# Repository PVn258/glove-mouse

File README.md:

# Glove Mouse

A wearable BLE HID mouse built on the **XIAO ESP32-C6**, controlled by wrist movement (MPU-6050 gyroscope) and finger sensors (flex + FSR pressure).

---

## Hardware

| Component | Role |
|-----------|------|
| XIAO ESP32-C6 | Main MCU + BLE |
| MPU-6050 | Gyroscope / accelerometer → cursor movement |
| Flex sensor | Thumb bend → toggle transmission mode |
| FSR (×2) | Left / right click |
| MT3608 boost | Battery → ~4.6 V rail for VIN |
| LM339 (×2) | Analog comparators for flex & FSR digital output |

### Wiring

```
MPU-6050   SDA → GPIO 6   |   SCL → GPIO 7
Flex  DO       → GPIO 4     (thumb bend = transmit mode)
FSR Left  DO   → GPIO 2     (left click)
FSR Right DO   → GPIO 3     (right click)
```

---

## Firmware

### Dependencies (install via Arduino IDE Library Manager)

- **NimBLE-Arduino** by h2zero `≥ 1.4.0`
- **MPU6050** by Electronic Cats

### Board setup

1. Add ESP32 board package URL in Arduino IDE preferences:
   ```
   https://raw.githubusercontent.com/espressif/arduino-esp32/gh-pages/package_esp32_index.json
   ```
2. Install **esp32** by Espressif Systems
3. Select board: **XIAO ESP32C6**

### Usage

1. Flash `glove_mouse/glove_mouse.ino`
2. Open Serial Monitor at **115200 baud**
3. Pair with **"Glove Mouse"** from your host's Bluetooth settings
4. **Bend thumb** → transmission mode (cursor follows wrist, FSR triggers clicks)
5. **Release thumb** → sleep mode (all input paused)

### Tuning parameters

| Constant | Default | Description |
|----------|---------|-------------|
| `MAX_MOVE` | 20 | Max pixels per frame (higher = more sensitive) |
| `MAX_DPS` | 200 | Gyro threshold for full speed (°/s) |
| `DEADZONE` | 5 | Dead zone in °/s (higher = less jitter) |
| `CURVE_EXP` | 1.5 | Speed curve exponent (1.0 = linear, >1 = precise low / fast high) |
| `EMA_ALPHA` | 0.25 | Smoothing factor (0.1 = very smooth, 0.4 = responsive) |

---

## Schematic & PCB Design

The circuit was drawn in **EasyEDA Pro** and exported for JLCPCB fabrication.

| File | Description |
|------|-------------|
| `hardware/ProPrj_Seeed Studio XIAO ESP32C6_2026-05-12_10-11-10_2026-05-13.epro2` | EasyEDA Pro project (editable source) |
| `hardware/SCH_Schematic1_2026-05-14.pdf` | Schematic PDF (quick reference) |

**PCB specs for JLCPCB ordering:**

| Parameter | Value |
|-----------|-------|
| Layers | 2 |
| Board size | 50 × 40 mm |
| Min trace / space | 0.2 mm / 0.2 mm |
| Min via drill | 0.4 mm |
| Surface finish | HASL (lead-free) |

---

## Repository Structure

```
glove_mouse/
└── glove_mouse.ino          Main BLE HID firmware

hardware/
├── *.epro2                  EasyEDA Pro schematic & PCB project
└── *.pdf                    Exported schematic PDF

tests/
├── all_sensors_test/        All sensors combined diagnostic
├── flex_sensor_test/        Flex sensor digital output test
├── mpu6050_test/            MPU-6050 I2C + gyro/accel readout
└── pressure_sensor_test/    FSR pressure sensor test
```

---

## Running the Tests

Each folder under `tests/` is a standalone Arduino sketch.  
Open the `.ino` file in Arduino IDE, select **XIAO ESP32C6**, upload, then open Serial Monitor at **115200 baud**.

| Sketch | What it prints |
|--------|---------------|
| `mpu6050_test` | Accel XYZ + Gyro XYZ raw values |
| `flex_sensor_test` | Digital output of flex comparator (0/1) |
| `pressure_sensor_test` | Digital output of left & right FSR (0/1) |
| `all_sensors_test` | All of the above combined |

---

## License

MIT

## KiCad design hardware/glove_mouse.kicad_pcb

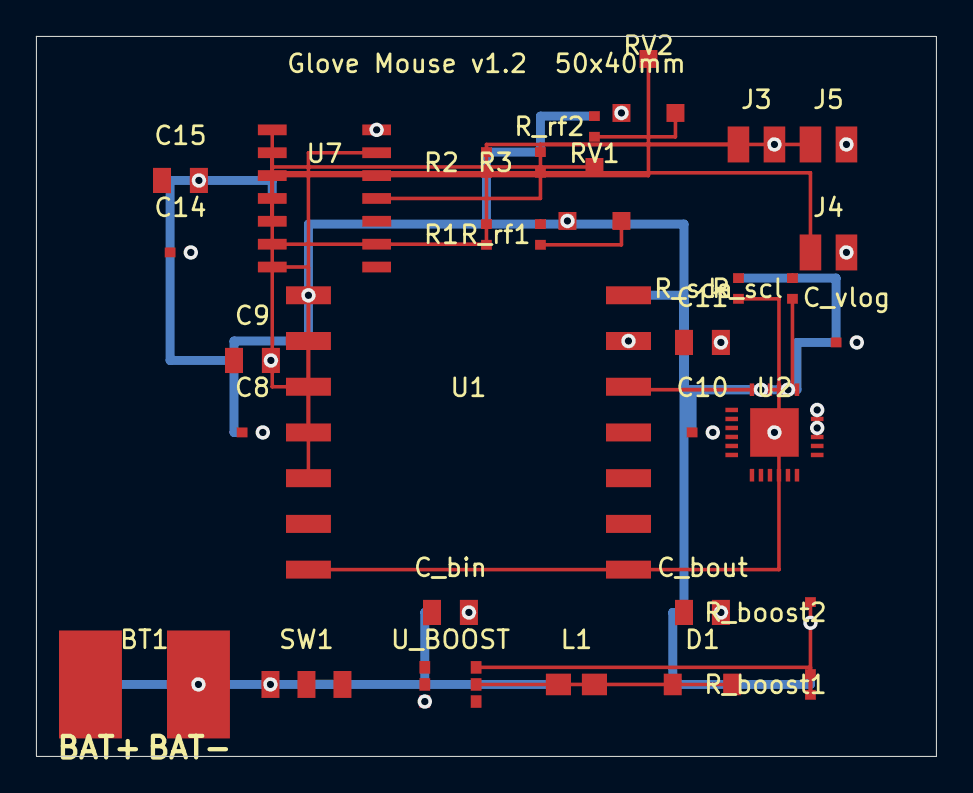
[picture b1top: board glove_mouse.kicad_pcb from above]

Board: 2 copper layers, 50.0 x 40.0 mm, 31 parts (0 on the bottom side), 19 nets.

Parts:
BT1: LiPo Battery; BAT-SOLDER
C8, C10, C14: 100nF; C_0402
C9: 22uF; C_0805
C11: 10uF; C_0805
C15: 4.7uF; C_0805
C_bin: 10uF; C_0805
C_bout: 22uF; C_0805
C_vlog: 100nF; C_0402
D1: SS14; SOD-123
J3: Flex; JST-PH-2P
J4: FSR Left; JST-PH-2P
J5: FSR Right; JST-PH-2P
L1: 4.7uH; L_0603
R1: 47k; R_0402
R2, R3: 10k; R_0402
RV1, RV2: 10k Trim; TRIMPOT-3224W
R_boost1: 100k; R_0402
R_boost2: 15k; R_0402
R_rf1, R_rf2: 10k; R_0402
R_scl: 4.7k; R_0402
R_sda: 4.7k; R_0402
SW1: Power SW; SLIDE-SW
U1: XIAO ESP32C6; XIAO-ESP32C6
U2: MPU-6050; QFN-24
U7: LM339; SOP-14
U_BOOST: MT3608; SOT-23-6

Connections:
3V3: C8.1, C9.1, C10.1, C11.1, C14.1, C15.1, C_vlog.1, R1.1, R2.1, R3.1, R_rf1.1, R_rf2.1, R_scl.1, R_sda.1, U1.2, U2.1, U2.6, U7.4
BAT_RAW: BT1.+, SW1.3
BOOST_FB: R_boost1.2, R_boost2.1, U_BOOST.4
BOOST_OUT: C_bout.1, D1.K, R_boost1.1, U1.8
BOOST_SW: D1.A, L1.2, U_BOOST.5
FLEX_DO: U1.5, U7.1
FSR_L_DO: U1.3, U7.7
FSR_R_DO: U1.4, U7.9
GND: BT1.-, C8.2, C9.2, C10.2, C11.2, C14.2, C15.2, C_bin.2, C_bout.2, C_vlog.2, J3.2, J4.2, J5.2, RV1.1, RV2.1, R_boost2.2, SW1.1, U1.1, U1.9, U2.2, U2.5, U2.7, U2.9, U2.25, U7.8, U_BOOST.1
SCL: R_scl.2, U1.10, U2.3
SDA: R_sda.2, U1.7, U2.4
VBAT: C_bin.1, L1.1, SW1.2, U_BOOST.2, U_BOOST.3
VMID_FLEX: J3.1, R1.2, U7.2
VMID_FSR_L: J4.1, R2.2, U7.5
VMID_FSR_R: J5.1, R3.2, U7.11
VREF_FLEX: RV1.W, U7.3
VREF_FLEX_PRE: RV1.3, R_rf1.2
VREF_FSR: RV2.W, U7.6, U7.10
VREF_FSR_PRE: RV2.3, R_rf2.2
